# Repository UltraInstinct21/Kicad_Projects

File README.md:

# Kicad_Projects
Kicad projects

1. Buck Converter
  To convert 24V to 12V , 5V 2A and 3.3V 2A.

2. Transmitter and Receiver
  A 7-channel transmitter and receiver using NRF24L01 and Arduino Nano.

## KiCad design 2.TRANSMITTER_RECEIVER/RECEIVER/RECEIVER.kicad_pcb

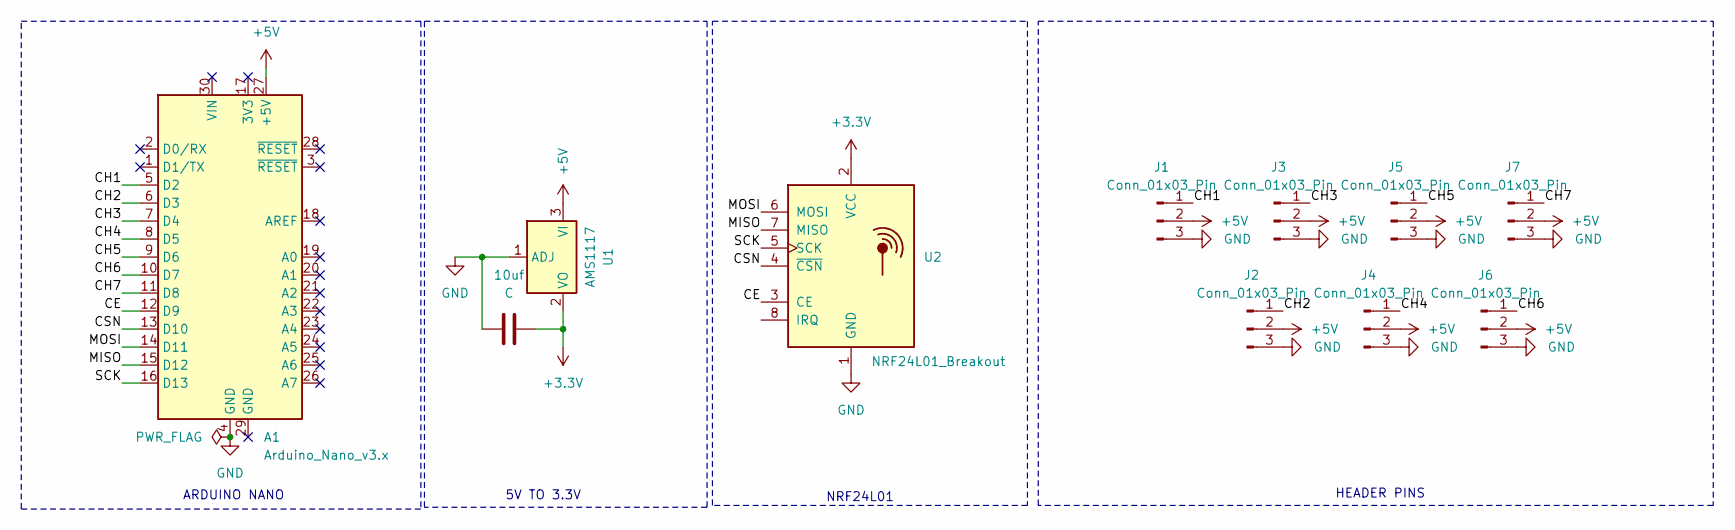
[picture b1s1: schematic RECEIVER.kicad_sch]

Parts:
10uf: C; C_Disc_D3.0mm_W1.6mm_P2.50mm
A1: Arduino_Nano_v3.x; Arduino_Nano
J1, J2, J3, J4, J5, J6, J7: Conn_01x03_Pin; PinHeader_1x03_P2.54mm_Vertical
U1: AMS1117; SOT-223-3_TabPin2
U2: NRF24L01_Breakout; nRF24L01_Breakout

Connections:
+3.3V: 10uf.2, U1.2 (VO), U2.2 (VCC); also elsewhere on the board
+5V: A1.27 (+5V), J1.2, J2.2, J3.2, J4.2, J5.2, J6.2, J7.2, U1.3 (VI)
/CE: A1.12 (D9), U2.3 (CE)
/CH1: A1.5 (D2), J1.1
/CH2: A1.6 (D3), J2.1
/CH3: A1.7 (D4), J3.1
/CH4: A1.8 (D5), J4.1
/CH5: A1.9 (D6), J5.1
/CH6: A1.10 (D7), J6.1
/CH7: A1.11 (D8), J7.1
/CSN: A1.13 (D10), U2.4 (~CSN)
/MISO: A1.15 (D12), U2.7 (MISO)
/MOSI: A1.14 (D11), U2.6 (MOSI)
/SCK: A1.16 (D13), U2.5 (SCK)
GND: 10uf.1, A1.4 (GND), J1.3, J2.3, J3.3, J4.3, J5.3, J6.3, J7.3, U1.1 (ADJ), U2.1 (GND); also elsewhere on the board

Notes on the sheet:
HEADER PINS
NRF24L01
5V TO 3.3V
ARDUINO NANO

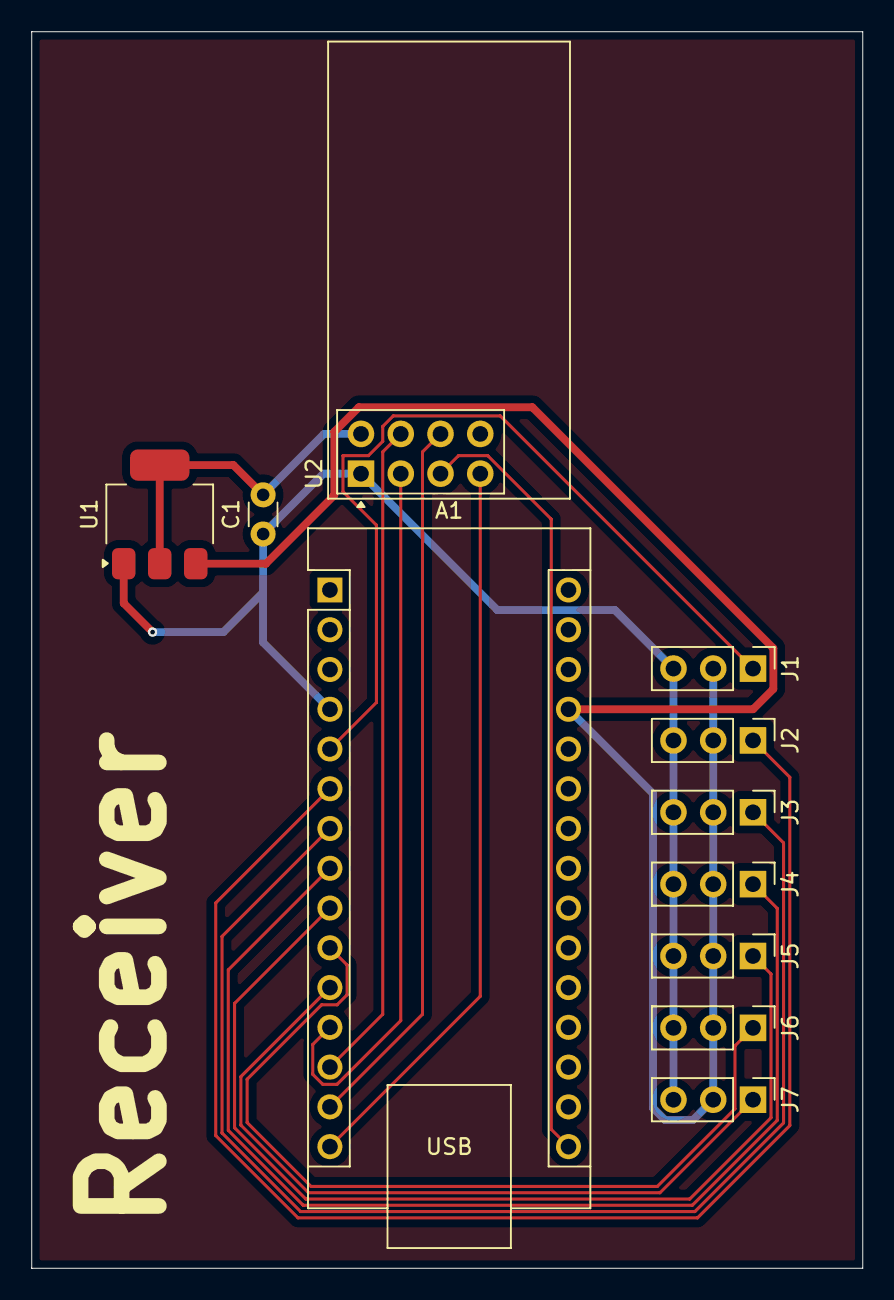
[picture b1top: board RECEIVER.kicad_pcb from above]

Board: 2 copper layers, 53.1 x 79.0 mm, 11 parts (0 on the bottom side), 15 nets.

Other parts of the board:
C1: C; C_Disc_D3.0mm_W1.6mm_P2.50mm

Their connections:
+3.3V: C1.2; also elsewhere on the board
GND: C1.1; also elsewhere on the board

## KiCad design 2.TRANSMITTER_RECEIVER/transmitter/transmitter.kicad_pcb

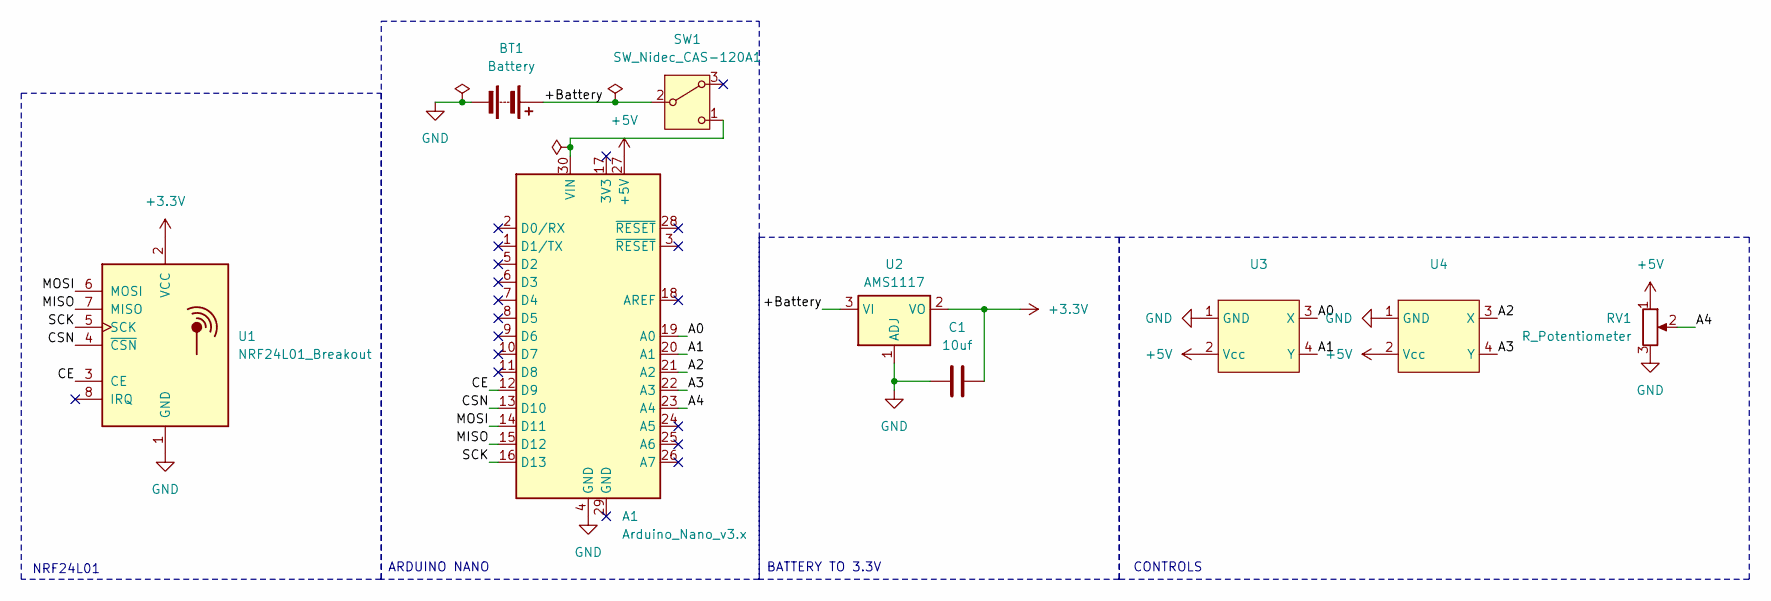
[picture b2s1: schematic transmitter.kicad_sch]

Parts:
A1: Arduino_Nano_v3.x; Arduino_Nano
BT1: Battery; BatteryHolder_MPD_BA9VPC_1xPP3
C1: 10uf; C_Radial_D4.0mm_H5.0mm_P1.50mm
RV1: R_Potentiometer; Potentiometer_Alps_RK09K_Single_Vertical
SW1: SW_Nidec_CAS-120A1; Nidec_Copal_CAS-120A
U1: NRF24L01_Breakout; nRF24L01_Breakout
U2: AMS1117; SOT-223-3_TabPin2
U3, U4: JOYSTICK-PSP1000

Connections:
+3.3V: C1.2, U1.2 (VCC), U2.2 (VO)
+5V: A1.27 (+5V), RV1.1, U3.2 (Vcc), U4.2 (Vcc)
/+Battery: BT1.1 (+), SW1.2 (B), U2.3 (VI)
/A0: A1.19 (A0), U3.3 (X)
/A1: A1.20 (A1), U3.4 (Y)
/A2: A1.21 (A2), U4.3 (X)
/A3: A1.22 (A3), U4.4 (Y)
/A4: A1.23 (A4), RV1.2
/CE: A1.12 (D9), U1.3 (CE)
/CSN: A1.13 (D10), U1.4 (~CSN)
/MISO: A1.15 (D12), U1.7 (MISO)
/MOSI: A1.14 (D11), U1.6 (MOSI)
/SCK: A1.16 (D13), U1.5 (SCK)
GND: A1.4 (GND), BT1.2 (-), C1.1, RV1.3, U1.1 (GND), U2.1 (ADJ), U3.1 (GND), U4.1 (GND)
unnamed: A1.30 (VIN), SW1.1 (C)

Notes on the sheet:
BATTERY TO 3.3V
NRF24L01
CONTROLS
ARDUINO NANO

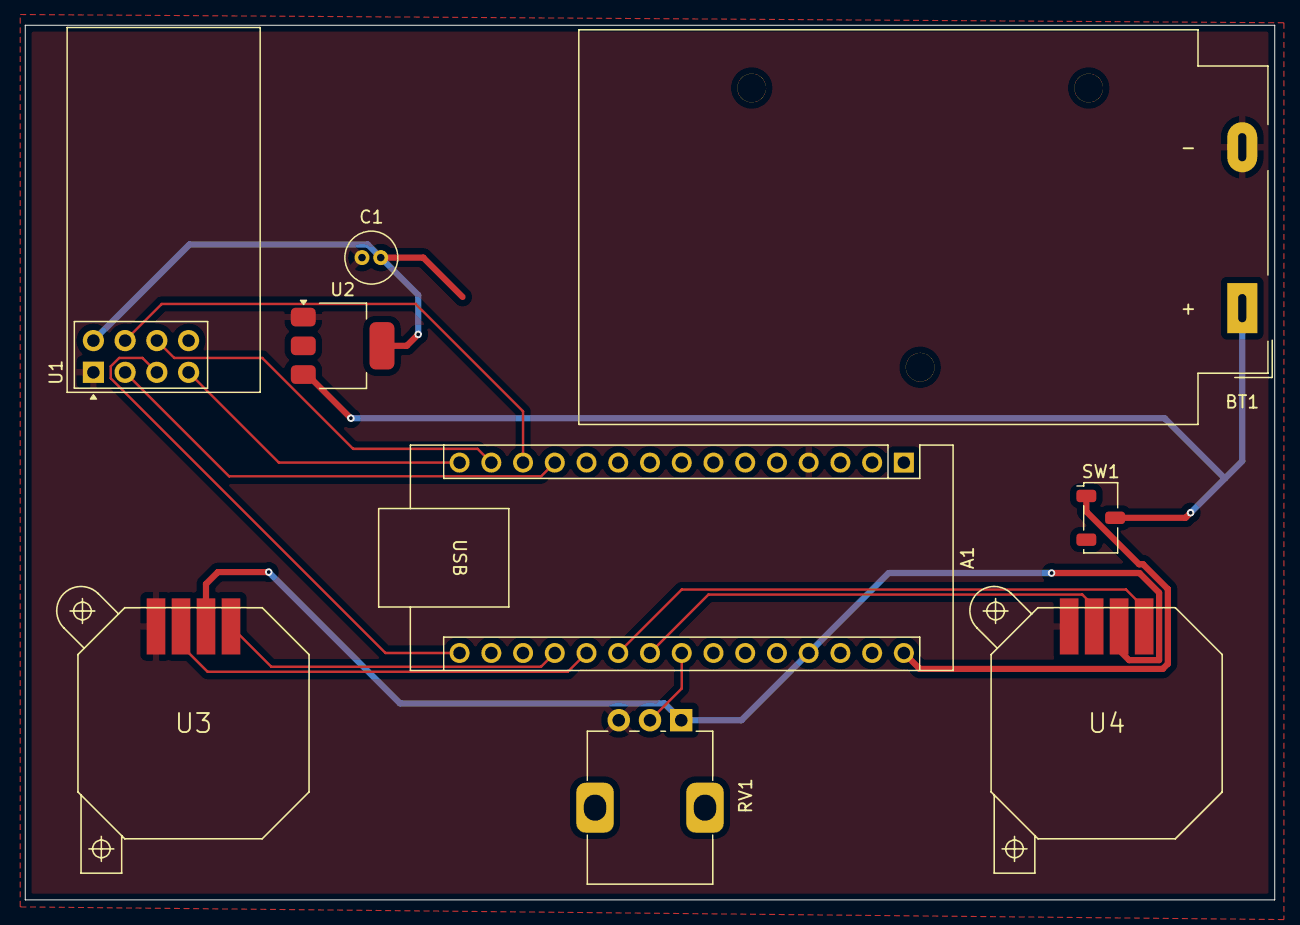
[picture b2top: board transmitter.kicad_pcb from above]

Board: 2 copper layers, 100.0 x 70.0 mm, 9 parts (0 on the bottom side), 15 nets.

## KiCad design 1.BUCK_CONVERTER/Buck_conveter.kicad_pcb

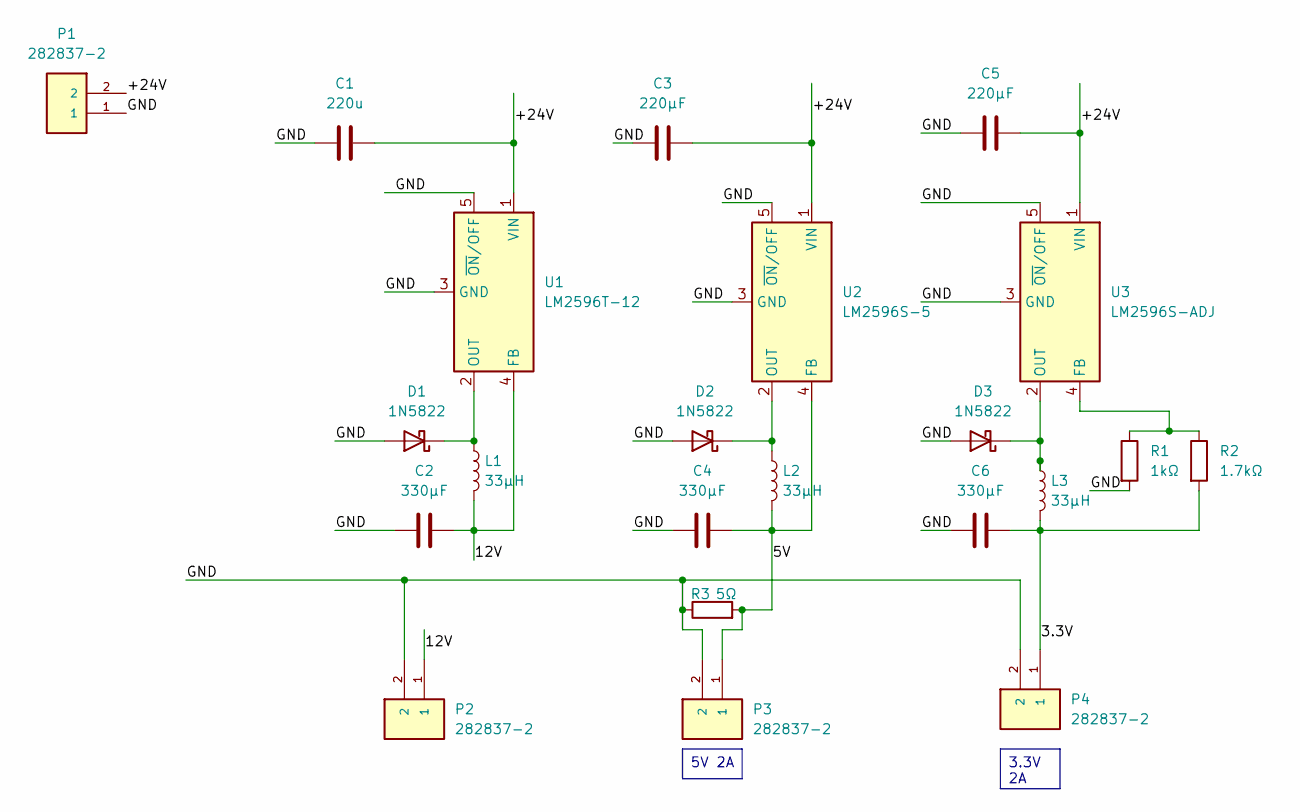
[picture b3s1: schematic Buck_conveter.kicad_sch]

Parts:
C1: 220u; C_Axial_L5.1mm_D3.1mm_P15.00mm_Horizontal
C2, C4, C6: 330μF; C_Axial_L5.1mm_D3.1mm_P15.00mm_Horizontal
C3, C5: 220μF; C_Axial_L5.1mm_D3.1mm_P15.00mm_Horizontal
D1, D2, D3: 1N5822; D_DO-201AD_P15.24mm_Horizontal
L1, L2, L3: 33µH; L_Axial_L5.0mm_D3.6mm_P10.00mm_Horizontal_Murata_BL01RN1A2A2
P1, P2, P3, P4: 282837-2; 2pin_screwterminal; PARTREV G3
R1: 1kΩ; R_Axial_DIN0207_L6.3mm_D2.5mm_P7.62mm_Horizontal
R2: 1.7kΩ; R_Axial_DIN0207_L6.3mm_D2.5mm_P7.62mm_Horizontal
R3: 5Ω; R_Axial_DIN0207_L6.3mm_D2.5mm_P7.62mm_Horizontal
U1: LM2596T-12; TO-220-5_P3.4x3.7mm_StaggerOdd_Lead3.8mm_Vertical
U2: LM2596S-5; TO-263-5_TabPin3
U3: LM2596S-ADJ; TO-263-5_TabPin3

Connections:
/3.3V: C6.2, L3.2, P4.1, R2.2
/5V: C4.2, L2.2, P3.1, R3.2, U2.4 (FB)
/12V: C2.2, L1.2, P2.1, U1.4 (FB)
/+24V: C1.2, C3.2, C5.2, P1.2, U1.1 (VIN), U2.1 (VIN), U3.1 (VIN)
/GND: C1.1, C2.1, C3.1, C4.1, C5.1, C6.1, D1.2 (A), D2.2 (A), D3.2 (A), P1.1, P2.2, P3.2, P4.2, R1.2, R3.1, U1.3 (GND), U1.5 (~ON/OFF), U2.3 (GND), U2.5 (~ON/OFF), U3.3 (GND), U3.5 (~ON/OFF)
unnamed: D1.1 (K), L1.1, U1.2 (OUT)
unnamed: D2.1 (K), L2.1, U2.2 (OUT)
unnamed: D3.1 (K), L3.1, U3.2 (OUT)
unnamed: R1.1, R2.1, U3.4 (FB)

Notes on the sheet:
3.3V 2A
5V 2A

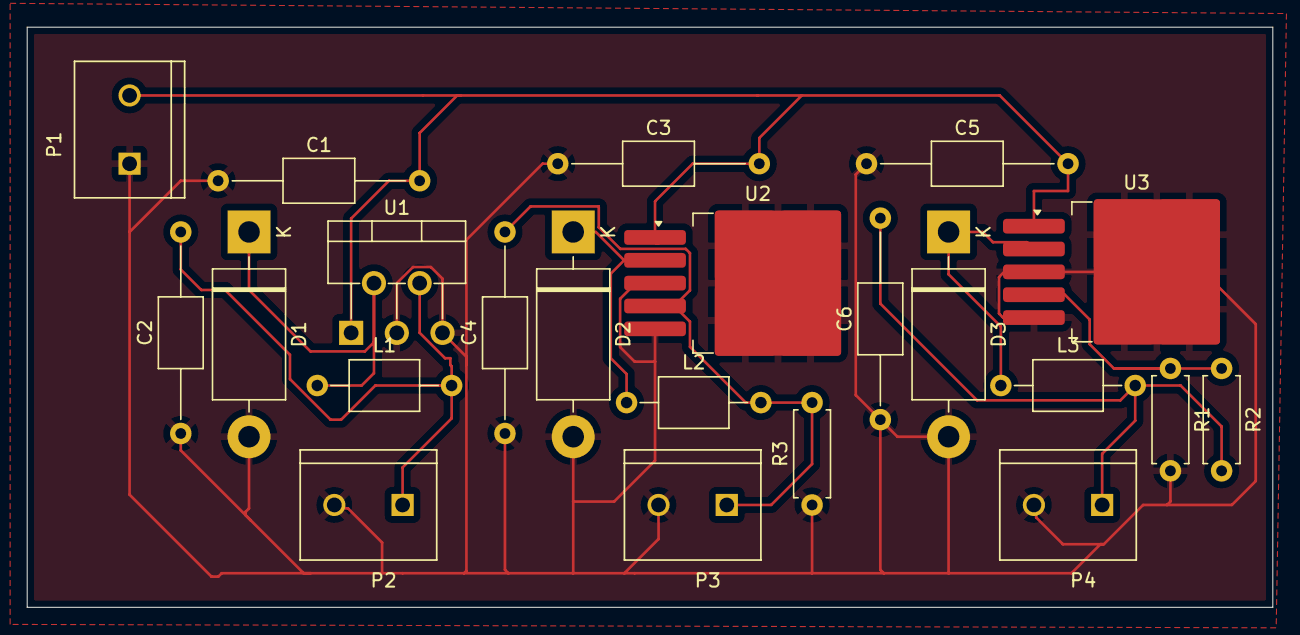
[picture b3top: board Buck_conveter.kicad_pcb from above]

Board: 2 copper layers, 92.7 x 43.2 mm, 22 parts (0 on the bottom side), 9 nets.

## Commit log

2025-08-27 README.md
